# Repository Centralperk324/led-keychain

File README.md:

[Uploading Allison Perkey 555 Timer PCB.kicad_pcb…]()
# LED-Ladybug-Keychain
This is my first legitimate project that I'm submitting, and it is a ladybug keychain connected to a 555 monostable timer that lights up my LED for 5 seconds after pressing a button. 

# Install
The PCB components need to be soldered together into the board, and it will fit directly inside my ladybug casing. A battery gets hooked up to the screw terminals and will hide underneath the PCB in the casing itself. 

# Using the Piece
The LED lights up when the pushbutton is pressed due to using a 555 monostable timer, and the button has a cutout in the casing for easy access. 

# Bill of Materials

|  Component  |  Quantity  |  Unit  |  Description  | 
|---------------------------------------------------|
| NE555 Chip  |      1     |        |Controls Timing|
|---------------------------------------------------|
| Resistor    |      2     |10k ohm |Limits Current |
|---------------------------------------------------|
| Resistor    |      1     |470 ohm |Limits Current |
|---------------------------------------------------|
| Red LED     |      1     |        |Lights up      |
|---------------------------------------------------|
| Capacitor   |      1     | 470uF  |Timing Limitor |
|---------------------------------------------------|
| Capacitor   |      1     | 100nF  |Energy Storage |
|---------------------------------------------------|
| Pushbutton  |      1     |       |Triggers circuit|
|---------------------------------------------------|
|6 Term Screw |            |     |Allows positive   |
| Terminals   |      2     | |& negative connections|
|---------------------------------------------------|
|9volt Battery|      1     |9 volts | Powers Circuit| 
|---------------------------------------------------|

# Files for PCB and Onshape Design
Schematic Design - 

PCB Design - 

Onshape Design -

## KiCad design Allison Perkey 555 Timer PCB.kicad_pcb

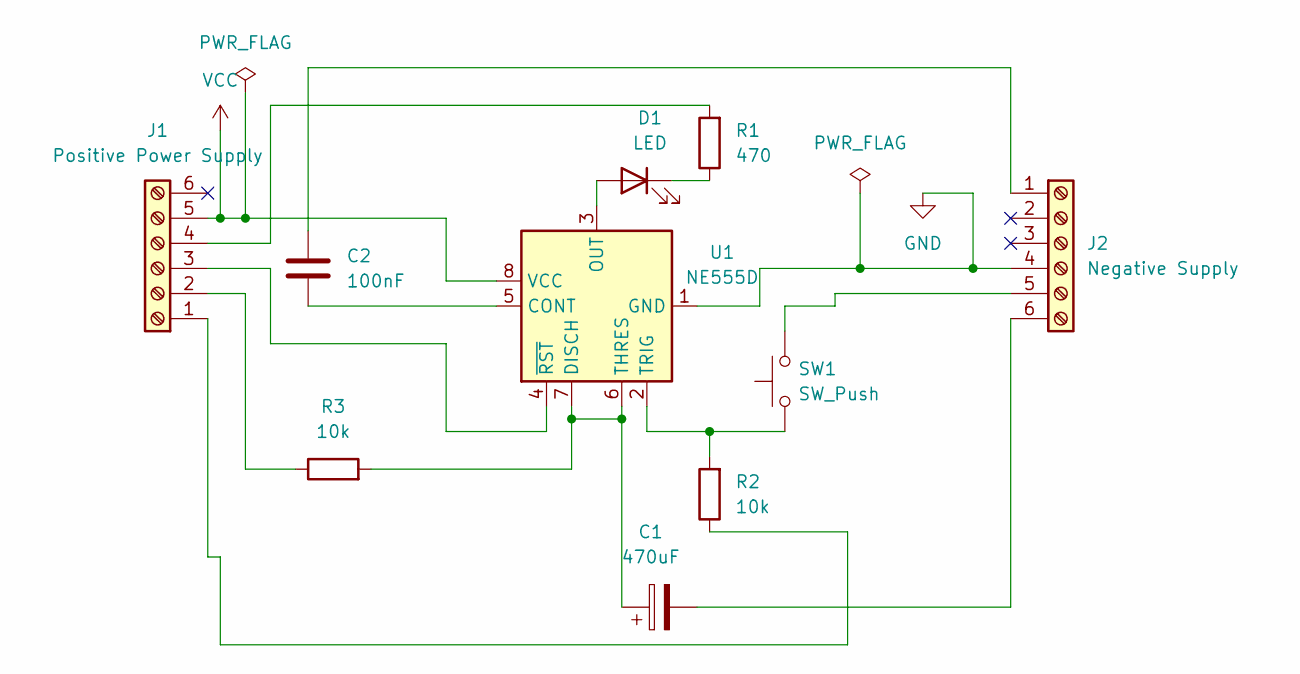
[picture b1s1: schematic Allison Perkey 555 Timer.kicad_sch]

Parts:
C1: 470uF; C_Radial_D10.0mm_H20.0mm_P5.00mm
C2: 100nF; C_Radial_D10.0mm_H20.0mm_P5.00mm
D1: LED; LED_D5.0mm
J1: Positive Power Supply; TerminalBlock_4Ucon_1x06_P3.50mm_Horizontal
J2: Negative Supply; TerminalBlock_4Ucon_1x06_P3.50mm_Horizontal
R1: 470; R_Axial_DIN0207_L6.3mm_D2.5mm_P10.16mm_Horizontal
R2, R3: 10k; R_Axial_DIN0207_L6.3mm_D2.5mm_P10.16mm_Horizontal
SW1: SW_Push; SW_Push_1P1T_NO_CK_KSC6xxJ
U1: NE555D; SOIC-8_3.9x4.9mm_P1.27mm

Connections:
GND: J2.4, U1.1 (GND)
unnamed: D1.2 (A), U1.3 (OUT)
unnamed: D1.1 (K), R1.1
unnamed: J1.1, R2.1
unnamed: J1.2, R3.1
unnamed: J1.3, U1.4 (~RST)
unnamed: J1.4, R1.2
unnamed: C2.1, J2.1
unnamed: J2.5, SW1.2
unnamed: C1.2, J2.6
unnamed: C2.2, U1.5 (CONT)
unnamed: C1.1, R3.2, U1.6 (THRES), U1.7 (DISCH)
unnamed: R2.2, SW1.1, U1.2 (TRIG)
VCC: J1.5, U1.8 (VCC)

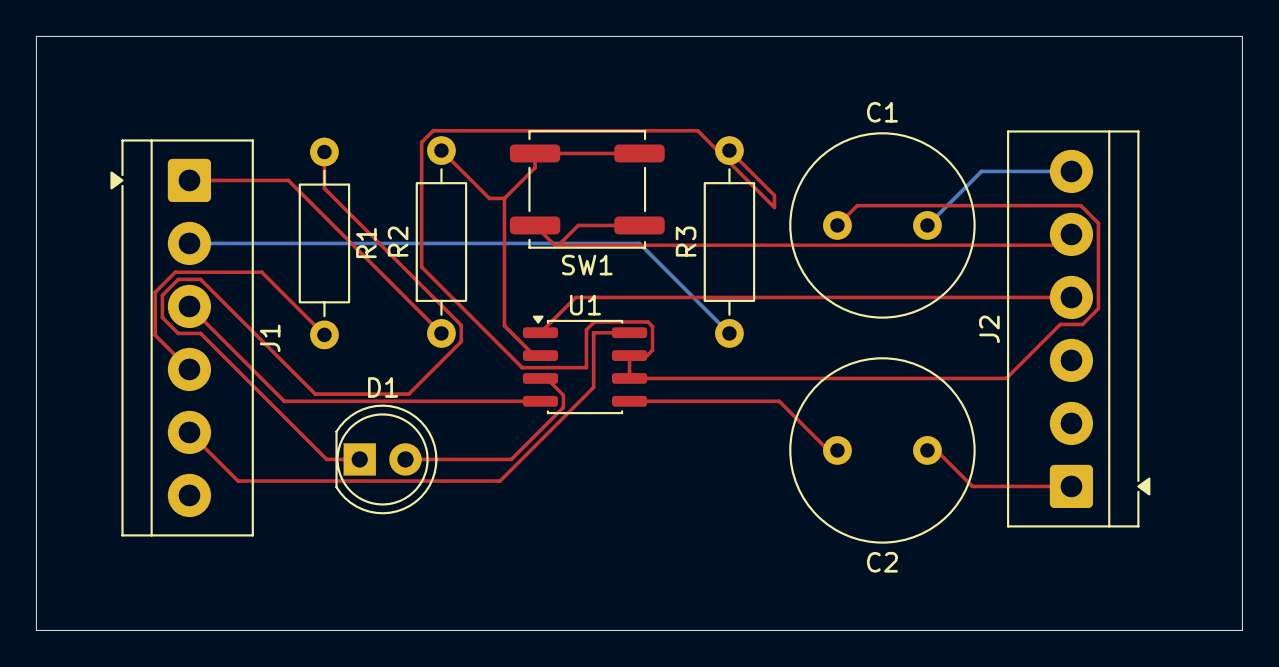
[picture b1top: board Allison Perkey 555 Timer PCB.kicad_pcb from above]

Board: 2 copper layers, 67.0 x 33.0 mm, 10 parts (0 on the bottom side), 14 nets.
